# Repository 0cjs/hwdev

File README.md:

hwdev: cjs's Hardware Development Repo
======================================

__Note for developers:__ Please run `Test` before committing. But also:
- In order to avoid a lot of spurious changes on dev branches, `Test` will
  update renders only if you are commiting to the `main` branch. On dev
  branches, if you want to see/test renders, just use the `render` script
  directly. Ensure you bring commits to `main` and run `Test` there before
  pushing them and test them on `main`.
- If you see massive changes to renders in all projects when you run
  `Test`, you are probably running a different version of KiCad than
  normally used with this repo. Check the `kicad-version` file for changes
  and, if lower, upgrade, or if higher, discuss with the repo owner.

#### General Files and Directores

- `Test`: Top-level test script.
- `bin/`: Support programs and scripts.
  - `bin/render`: Given paths to `.kicad_sch` and `.kicad_pcb` files,
    renders PDF and Gerber versions of these to a `render/` dir at the same
    level as the directory containing the sch/pcb files. Run `bin/render -h`
    for more details.
  - `bin/ghdl-url`: Given a path to a file in a repo, return the fully
    resolved (i.e., not HTTP 302 redirects) GitHub download URL for it.
    (See the header comments in the file for more detail.)
- `kicad-version`: The version of KiCad used in the commit.
- `kicad-lib`: Contains the `0cjs-hwdev` KiCad symbol library, mainly
  vintage parts.

#### Project Directories

- [`drom`]: Ideas for a diode-ROM board.
- [`floppy-head-protector`]: PCB-only project to build a template to cut
  out cardboard head travel protectors for 5.25" floppy diskette drives.
- [`kp25tk`]: Configurable 25-key parallel keypad, with additional reset
  button and slide switch. The primary use is as a hex keypad interface to
  trainer boards, but it can serve a wide variety of purposes.
- [`rc6800`]: Variant of the RC6502 bus design, which is in turn a variant of
  the RC2014 bus.
- [`romread-adapter`]: Interface to allow reading of ROMs via the 8265
  PPI GPIO interface on a SuperAKI-80 SBC (or other similar system).
- [`romext-2364`]: A 2764 EPROM in this board outside the system is
  connected via a cable as a 2364 ROM in a socket in the system.
- [`tk85`]: Projects for the NEC TK-85 trainer board.

Project Files and Subdirectories
--------------------------------

Projects generally include the following files and subdirectories:
- `REAMDE.md`: A description of the project.
- `vis/`: Original diagrams, photos and other illustrations and
  visualisations of the project.
- `kicad/`: The KiCad design files (`.kicad_pro`, `.kicad_sch`, etc.).
- `render/`: Renderings from the KiCad design files, including a PDF of the
  schematic and Gerbers of the board design. These are usually generated
  via the top-level `render` script but may be created manually; see above.
  (Also see below about viewing board designs.)

### Revision Numbers

Project use revisions int the format _S-B_ where _S_ is the schematic
revision and _B_ is the board revision within that scheamtic. Either number
being suffixed with `dev` indicates that it's a development revision
heading towards that next revision, e.g., `2dev-3` is development towards
revision `2` of the schematic. (Revision `0` is always considered a
development revision towards revision `1`.)

The revision number is separately set and updated (in _File » Page
Settings…_) for the schematic and PCB. If you change the schematic from `2`
to `3` you will then manually need to change the PCB to from `2-3` to
`3-4dev`.

Release versions are tagged in Git with the project name and release,
separated by an underscore, e.g. `kp25tk_2-1`.

### Viewing Board Designs

The `$PROJECT/render/$PROJECT-jlcpcb.zip` contains a subset of Gerbers
designed for upload to [JLCPCB]. This file also serves as a way to view the
board design without having to load up KiCad: you can upload this file to
any of several web-based Gerber viewers. These include:

* __[PCBWay viewer]:__ Press the '+' button and upload the ZIP. Provides
  Gerber layers and 2D top and bottom board views. Saves the uploads so you
  need not upload again if you come back later.

* __[JLCPCB viewer]:__ Requires sign-in. Click "Add gerber file" at the
  middle left of the top page (or at the top of the order page) and then
  click "Gerber Viewer" at the lower right just below the small renders.
  provides Gerber layers and both 2D top/bottom 3D board renders.

* __[NextPCB viewer]:__ Click "Upload Files" and upload the ZIP. Provides
  Gerber layer views, error checking, and a PDF report download that
  includes 2D top/ bottom board views.

* __[Tracespace viewer]:__ An [open source][tracespace] viewer that can
  accept URLs to ZIP files of Gerbers. (This has been re-used by several
  PCB house websites and others.) Unfortunately, it does not follow HTTP
  302 redirects, so it doesn't work with "raw download" links from GitHub;
  you need to convert them to the `githubusercontent.com` link with
  the `bin/ghdl-url` program. Also, unfortunately, there seems to be no way
  to specify the download URL in a query string to have it automatically
  load the data by clicking on a link.

Viewers confirmed not to work with the ZIP file include the __[Altium 365
viewer].__ (These may work by uploading the individual files under the
`render/$PROJECT-gerber/` directory.)

<!-------------------------------------------------------------------->
[`drom`]: ./drom/
[`floppy-head-protector`]: ./floppy-head-protector/
[`kp25tk`]: ./kp25tk/
[`rc6800`]: ./rc6800/
[`romread-adapter`]: ./romread-adapter/
[`romext-2364`]: ./romext-2364/
[`tk85`]: ./tk85/

[Altium 365 viewer]: https://www.altium.com/viewer/
[JLCPCB viewer]: https://cart.jlcpcb.com/quote
[JLCPCB]: https://jlcpcb.com/
[NextPCB viewer]: https://www.nextpcb.com/free-online-gerber-viewer.html
[PCBWay viewer]: https://www.pcbway.com/project/OnlineGerberViewer.html
[Tracespace viewer]: https://tracespace.io/view/
[tracespace]: https://github.com/tracespace/tracespace

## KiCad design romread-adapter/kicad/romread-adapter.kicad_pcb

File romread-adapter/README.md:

ROM Reading Adapter
===================

You can download [the schematic in PDF format][dl-sch] and [a ZIP of the
Gerbers][dl-jlc]. The latter has been tested with JLCPCB, and you can also
give that URL to [tracespace.io] to view them.

This board allows a host device to read up to 42-pin through-hole DIP ROMs
with any arbitrary pinout. The host device will typically be a computer
that can supply ground and +5V, and has at least two Intel [8255] PPIs
(Programmable Peripheral Interface chips) that will be connected to the
address, data and select pins of the ROM.

The header is designed to connect to the the CN3 connector of an
[SuperAKI-80 SBC], connecting it to the 8265 that provides the equivalent
of two 8255 chips. However, via different cables and adapters (supplied by
the user) it can be connected to any system providing equivalent
functionality.

Usage
-----

The board has three main parts.

#### ZIF Socket

The ROM should be inserted in at the bottom of the 42-pin ZIF socket at the
left, with pin 1 towards the top.

#### Workspace Area

The centre of the board is the workspace area, consisting of two columns of
.1" header pins connected to the pins of the ROM device in the ZIF socket
("ROM pins") and separate pins connected to the address outputs, positive
and negative chip select outputs, and data inputs of the host device ("host
pins"). Between these two columns the silk screen indicates the pin numbers
for 24-, 28- and 32-pin ROM devices.

The 23 pins directly adjacent to the ZIF socket pins are "default pins,"
host pins assigned per the JEDEC standard pinouts for 24- and 28-pin ROMs
and EPROMs. When reading common devices, you can use jumpers to connect
these to the adjacent ROM pins; these typically will not need to be changed
unless you're reading a non-JEDEC device.

ROM pins pins without an adjacent default pin either have functions varying
between JEDEC standard ROM devices or there is no JEDEC common default for
them. These should be connected with "dupont" jumper wires to the headers
around the edge of the board that give access to ground, +5V, positive and
negative chip select outputs, address outputs, and data inputs.

#### Host Header

The host header connects the host via a 50-pin ribbon cable. For a
SuperAKI-80 board this can be connected directly to the CN3 connector; for
other boards you'll need to wire your own cable or adapter.

For the SuperAKI-80, the connections are as follows:

    SuperAKI-80     ROM Reader Board Host Signals
    ────────────────────────────────────────────────────────────
    VCC             VCC
    GND             GND
    PPI 0-A 0-7     A0-A7
    PPI 0-B 0-7     A8-A15
    PPI 0-C 0-3     A16-A19
            4,5     n/c
            6       CS (positive logic chip select)
            7       C̅S̅ (negative-logic chip select)
    PPI 1-A 0-7     D0-D7
    PPI 1-B 0-7     D9-D14
    PPI 1-C 0-7     n/c

#### Software

Software to read ROMs has not yet been developed.

Design Notes
------------

### PCB DRC Warnings and Exclusions

A number of PCB DRC warnings are ignored. The reasons are:
- "Adjacent header pins" courtyard overlaps on JR2 and JR3: In the work
  area the header pins intended for use with "default" jumpers for most
  ROMs the headers must be side by side in order to place the jumpers
  acrosss the pins.
- "Work area default jumpers" silkscreen overlap on JR2 and JR3: As with
  the work area header pins courtyard overlaps above.
- "ZIF socket at edge" silkscreen off edge of board: The ZIF socket is at
  the left edge of the board, causing a bit of the left edge of silk screen
  for the lever hinge to be cut off. This isn't a problem; enough is still
  there that the placement of the ZIF socket is clear.

<!-------------------------------------------------------------------->
[dl-jlc]: https://raw.githubusercontent.com/0cjs/hwdev/dev/cjs/25g03/rom-read-adapter/romread-adapter/render/romread-adapter-jlcpcb.zip
[dl-sch]: https://raw.githubusercontent.com/0cjs/hwdev/dev/cjs/25g03/rom-read-adapter/romread-adapter/render/romread-adapter-sch.pdf
[tracespace.io]: https://tracespace.io/view/

[SuperAKI-80 SBC]: https://akizukidenshi.com/goodsaffix/A003_SuperAKI-80.pdf
[8255]: https://en.wikipedia.org/wiki/Intel_8255

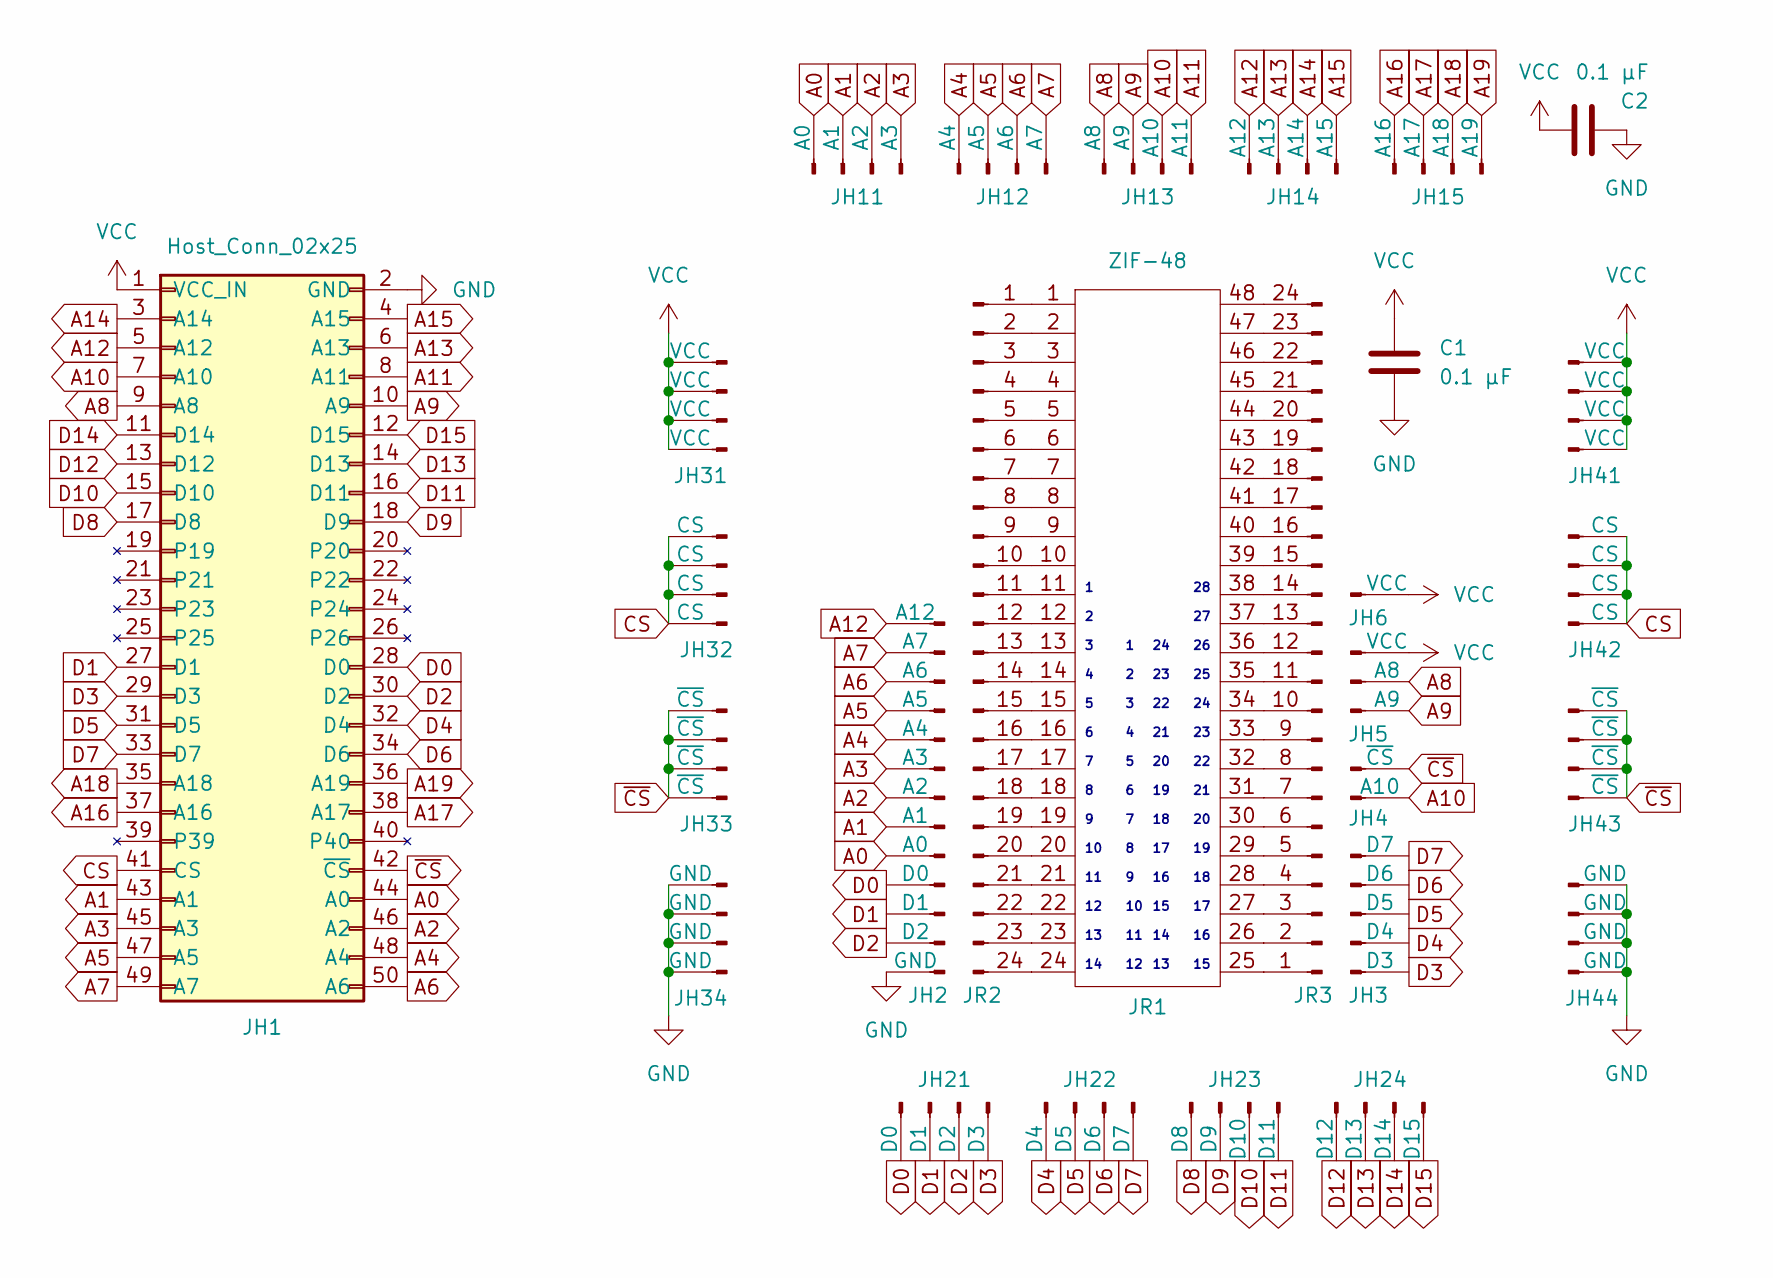
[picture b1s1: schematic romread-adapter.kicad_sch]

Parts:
C1, C2: 0.1 μF; C_Axial_L3.8mm_D2.6mm_P10.00mm_Horizontal
JH1: Host_Conn_02x25; PinHeader_2x25_P2.54mm_Vertical
JH2: Conn_01x13_Pin; PinHeader_1x13_P2.54mm_Vertical
JH3: Conn_01x05_Pin; PinHeader_1x05_P2.54mm_Vertical
JH4: Conn_01x02_Pin; PinHeader_1x02_P2.54mm_Vertical
JH5: Conn_01x03_Pin; PinHeader_1x03_P2.54mm_Vertical
JH6: Conn_01x01_Pin; PinHeader_1x01_P2.54mm_Vertical
JH11, JH12, JH13, JH14, JH15, JH21, JH22, JH23, JH24, JH31, JH32, JH33, JH34, JH41, JH42, JH43, JH44: Conn_01x04_Pin; PinHeader_1x04_P2.54mm_Vertical
JR1: ZIF-48; DIP_Socket-48_W11.9_W12.7_W15.24_W17.78_W18.5
JR2, JR3: Conn_01x24_Pin; PinHeader_1x24_P2.54mm_Vertical

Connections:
A0: JH1.44 (A0), JH2.9 (A0), JH11.1 (A0)
A1: JH1.43 (A1), JH2.8 (A1), JH11.2 (A1)
A2: JH1.46 (A2), JH2.7 (A2), JH11.3 (A2)
A3: JH1.45 (A3), JH2.6 (A3), JH11.4 (A3)
A4: JH1.48 (A4), JH2.5 (A4), JH12.1 (A4)
A5: JH1.47 (A5), JH2.4 (A5), JH12.2 (A5)
A6: JH1.50 (A6), JH2.3 (A6), JH12.3 (A6)
A7: JH1.49 (A7), JH2.2 (A7), JH12.4 (A7)
A8: JH1.9 (A8), JH5.2 (A8), JH13.1 (A8)
A9: JH1.10 (A9), JH5.1 (A9), JH13.2 (A9)
A10: JH1.7 (A10), JH4.1 (A10), JH13.3 (A10)
A11: JH1.8 (A11), JH13.4 (A11)
A12: JH1.5 (A12), JH2.1 (A12), JH14.1 (A12)
A13: JH1.6 (A13), JH14.2 (A13)
A14: JH1.3 (A14), JH14.3 (A14)
A15: JH1.4 (A15), JH14.4 (A15)
A16: JH1.37 (A16), JH15.1 (A16)
A17: JH1.38 (A17), JH15.2 (A17)
A18: JH1.35 (A18), JH15.3 (A18)
A19: JH1.36 (A19), JH15.4 (A19)
CS: JH1.41 (CS), JH32.1 (CS), JH32.2 (CS), JH32.3 (CS), JH32.4 (CS), JH42.1 (CS), JH42.2 (CS), JH42.3 (CS), JH42.4 (CS)
D0: JH1.28 (D0), JH2.10 (D0), JH21.1 (D0)
D1: JH1.27 (D1), JH2.11 (D1), JH21.2 (D1)
D2: JH1.30 (D2), JH2.12 (D2), JH21.3 (D2)
D3: JH1.29 (D3), JH3.1 (D3), JH21.4 (D3)
D4: JH1.32 (D4), JH3.2 (D4), JH22.1 (D4)
D5: JH1.31 (D5), JH3.3 (D5), JH22.2 (D5)
D6: JH1.34 (D6), JH3.4 (D6), JH22.3 (D6)
D7: JH1.33 (D7), JH3.5 (D7), JH22.4 (D7)
D8: JH1.17 (D8), JH23.1 (D8)
D9: JH1.18 (D9), JH23.2 (D9)
D10: JH1.15 (D10), JH23.3 (D10)
D11: JH1.16 (D11), JH23.4 (D11)
D12: JH1.13 (D12), JH24.1 (D12)
D13: JH1.14 (D13), JH24.2 (D13)
D14: JH1.11 (D14), JH24.3 (D14)
D15: JH1.12 (D15), JH24.4 (D15)
GND: C1.2, C2.2, JH1.2 (GND), JH2.13 (GND), JH34.1 (GND), JH34.2 (GND), JH34.3 (GND), JH34.4 (GND), JH44.1 (GND), JH44.2 (GND), JH44.3 (GND), JH44.4 (GND)
unnamed: JR1.1, JR2.1
unnamed: JR1.2, JR2.2
unnamed: JR1.3, JR2.3
unnamed: JR1.4, JR2.4
unnamed: JR1.5, JR2.5
unnamed: JR1.6, JR2.6
unnamed: JR1.7, JR2.7
unnamed: JR1.8, JR2.8
unnamed: JR1.9, JR2.9
unnamed: JR1.10, JR2.10
unnamed: JR1.11, JR2.11
unnamed: JR1.12, JR2.12
unnamed: JR1.13, JR2.13
unnamed: JR1.14, JR2.14
unnamed: JR1.15, JR2.15
unnamed: JR1.16, JR2.16
unnamed: JR1.17, JR2.17
unnamed: JR1.18, JR2.18
unnamed: JR1.19, JR2.19
unnamed: JR1.20, JR2.20
unnamed: JR1.21, JR2.21
unnamed: JR1.22, JR2.22
unnamed: JR1.23, JR2.23
unnamed: JR1.24, JR2.24
unnamed: JR1.25, JR3.1 (Pin_25)
unnamed: JR1.26, JR3.2 (Pin_26)
unnamed: JR1.27, JR3.3 (Pin_27)
unnamed: JR1.28, JR3.4 (Pin_28)
unnamed: JR1.29, JR3.5 (Pin_29)
unnamed: JR1.30, JR3.6 (Pin_30)
unnamed: JR1.31, JR3.7 (Pin_31)
unnamed: JR1.32, JR3.8 (Pin_32)
unnamed: JR1.33, JR3.9 (Pin_33)
unnamed: JR1.34, JR3.10 (Pin_34)
unnamed: JR1.35, JR3.11 (Pin_35)
unnamed: JR1.36, JR3.12 (Pin_36)
unnamed: JR1.37, JR3.13 (Pin_37)
unnamed: JR1.38, JR3.14 (Pin_38)
unnamed: JR1.39, JR3.15 (Pin_39)
unnamed: JR1.40, JR3.16 (Pin_40)
unnamed: JR1.41, JR3.17 (Pin_41)
unnamed: JR1.42, JR3.18 (Pin_42)
unnamed: JR1.43, JR3.19 (Pin_43)
unnamed: JR1.44, JR3.20 (Pin_44)
unnamed: JR1.45, JR3.21 (Pin_45)
unnamed: JR1.46, JR3.22 (Pin_46)
unnamed: JR1.47, JR3.23 (Pin_47)
unnamed: JR1.48, JR3.24 (Pin_48)
VCC: C1.1, C2.1, JH1.1 (VCC_IN), JH5.3 (VCC), JH6.1 (VCC), JH31.1 (VCC), JH31.2 (VCC), JH31.3 (VCC), JH31.4 (VCC), JH41.1 (VCC), JH41.2 (VCC), JH41.3 (VCC), JH41.4 (VCC)
~CS: JH1.42 (~CS), JH4.2 (~CS), JH33.1 (~CS), JH33.2 (~CS), JH33.3 (~CS), JH33.4 (~CS), JH43.1 (~CS), JH43.2 (~CS), JH43.3 (~CS), JH43.4 (~CS)

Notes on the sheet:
28 27 26 25 24 23 22 21 20 19 18 17 16 15
1 2 3 4 5 6 7 8 9 10 11 12
24 23 22 21 20 19 18 17 16 15 14 13
1 2 3 4 5 6 7 8 9 10 11 12 13 14

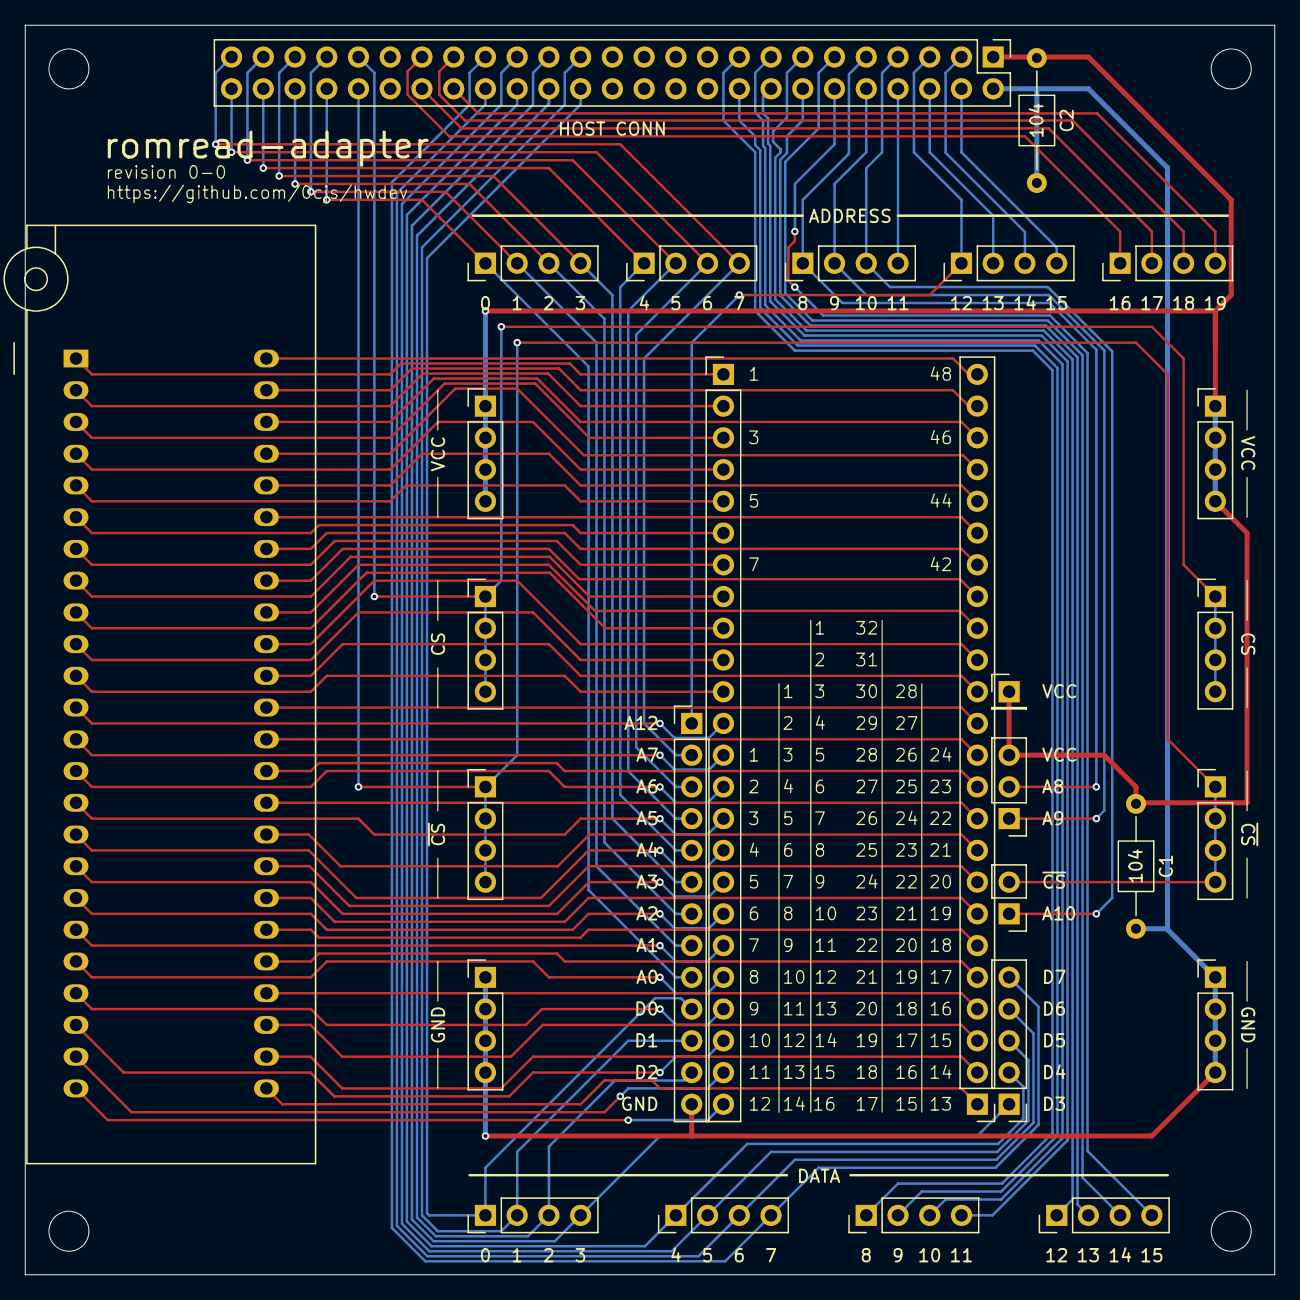
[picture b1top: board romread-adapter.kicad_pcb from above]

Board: 2 copper layers, 100.0 x 100.0 mm, 28 parts (0 on the bottom side), 88 nets.

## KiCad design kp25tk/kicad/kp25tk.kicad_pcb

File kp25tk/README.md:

KP25TK: 25-key Hex Keyboard
===========================

For ease of reference, this repository includes a `render/` subdirectory
containing some files generated from the `kicad/` files. __Bump version
numbers and regenerate these if you change the KiCad source.__
- [`kp25tk-sch.pdf`]: Schematic, generated via `File » Plot…` to PDF output.
- [`kp25tk-pcb.pdf`]: PCB, generated via File » Print…, enabling all layers,
  setting to portrait format and then printing to a file.
- [`kp25tk-render.png`]: PCB 3D render.
- [`kp25tk-silkscreen.png`]:
- [`kp25tk-tracks.png`]:

Contents:
- [Description](#description)
  - [Connections](#connections)
- [Components](#components)
  - [Key Swiches](#key-switches)
- [Theory of Operation](#theory-of-operation)
  - [Power Inputs](#power-inputs)
  - [Keypad Matrix](#keypad-matrix)
  - [NMI, Reset and Slide Switch Outputs](#nmi-reset-and-slide-switch-outputs)

Description
-----------

This 25-key 5×5 keyboard is similar to that on the [NEC TK-85].
with the following features.

* Power: +5V Vcc and GND from host system
* Matrix:
  - 3 row select input: ground one row to select
  - 8 row column output: rows pulled up to Vcc and pulled down by switch
  - 4×4 layout for hex digits `0` to `F`
  - 4 keys at the top and 4 keys at the right for commands
* 3 independent debounced switches:
  - Debounce time can be configured by changing a resistor value (see below).
  - All 3 provide positive and negative logic outputs.
  - 1 key at upper right hand corner of switch array for NMI interrupt
  - 1 tactile switch for RESET
  - 1 slide switch for a user-selected function

### Connections

The board is connected to the scanning device via a 2 row × 13 column
.1"-pitch male header ("Host"), usually used with a ribbon cable and IDC
female connector. The header is unshrouded to allow the use of smaller than
13 column connectors when the full 26 pins are not needed. (Though we
suggest _always_ using a 26P connector on the keypad side and simply using
a narrower ribbon cable that does not take up the full width of the
connector.)

The connector pin layout is configured via wire-wrapping or jumpering (with
"dupont" female-female jumper wires) individual 1-row header pins for each
function group to a second 2×13 header ("Config") that parallels the first.
This allows setting the ribbon cable connector pinout to match a wide
variety of scanning devices. The function groups are:

* Power input: 2:GND, 1:+5V
* Row select input: 3:row 2, 2:row 1, 1:row 0
* Column output: 8:column 7, ..., 1:column 0
* NMI key output: 2:/NMI (negative logic), 1:NMI (positive logic)
* RESET button output: 2:/RESET (negative logic), 1:RESET (positive logic)
* Slide switch output:
  -   UP: 2=low, 1=high
  - DOWN: 2=high, 1=low

### Design Goals

- Be fully configurable so it can work with almost any system.
- Do configuration in a way that it can be changed later.
- Provide a full hex keypad with additional keys for functions and some
  debounced switches for direct (non-scanned) functions.
- Have a physical layout that parallels the logical layout in order to make
  tracing the operation (whether for understanding or debugging) as easy as
  possible, even for novices to electronics.
- Use only through-hole parts to make soldering and modification as easy as
  possible.
- Be as compact as reasonably possible while meeting the other goals above.

Components
----------

### Key Switches

Currently planned are [Outemu "Tactile Brown"][keysw] (AliExpress) key
switches, which are (allegedly) compatible with Cherry MX and "CIY"
sockets.

These [Kailh switch sockets][kailh] (Adafruit) for MX-compatible mechanical
keys may be useful. They still need mechanical support, but the Adafruit
description says that a bit of hot glue or epoxy will do the trick.

Theory of Operation
-------------------

Component Summary:
- C[123], R[123], D[123], U1: Debounce and inversion circuitry for the
  `NMI` key, `RESET` button, and slide `SWITCH`, respectively.
- R[45], D[45]: Current-limiting resistors and LEDs for `PWR` (Vcc/GND
  present) and `SWLED` (slide switch ON) indicators, respectively.

### Host Connector and Configuration Headers

The 2×13 pin __Host__ header is connected to the host that will scan the
keypad. This is typically done with a ribbon cable with IDC connectors on
each end. Not all 26 pins need be used, but to help avoid pin interference
and misconnections it's best to use a 26-pin IDC connector on the keypad
end of the cable, even if a ribbon cable with fewer conductors is used.

The 2×13 __Config__ header pins are connected to the same-numbered Host
header pins; the builder needs to connect these to the function group
pins below. Wire-wrap is the most reliable way of doing this, but jumper
wires with "dupont"-style female connectors may also be used.

### Power Inputs

GND and +5V must be supplied from the host. (This is normally supplied
on the Host header, and then wired from the Config header to the `VCC_IN`
and `GND_IN` header pins.)

+5V is used to power the Schmitt inverters that debounce and invert the NMI
key, RESET button and slide switch. If only the keypad (less NMI key) is
used, +5V is not necessary.

A current-limiting resistor R4 (1K5) and power LED D4 indicate that the
board is powered. The current-limiting resistor is relatively high value so
that the LED isn't distractingly bright.

### Keypad Matrix

Each of the three row select inputs, `ROWSEL0`, `ROWSEL1`, `ROWSEL2`
connects to the corresponding row line for the keypad. When scanning, each
row in turn is driven low by the host, which then scans that row using the
column outputs.

Each column line is pulled high by its pull-up resistor when no key in that
column is pressed; this will read as `1` on the corresponding column output.
When a key in a _non-scanned_ row (row high or floating) is pressed, this
does not change. When a key in the _scanned_ row is pressed, the low row
sinks current through the diode and the closed keyswitch, bringing the
column low.

#### Keypad Pull-up Resistor Values

The keypad relies on the ability of the host driving the row select inputs
to to pull them down to 0 V, and do so reasonably quickly. Host drivers'
ability to do this varies, and the additional capacitance introduced by the
wiring connecting the keypad to the host, and the keys themselves, can
degrade this.

The 22K values chosen for the resistors give a fairly weak pull-up that's
still higher than other designs without a cable between the keyboard row
drivers and column inputs of the host. The resistor pack is in a socket to
allow changing the value.

If you are getting intermittent or no response from pressing keys, the
pull-up is too strong and you should try a _higher_ resistance, such as 33K
or 47K.

If you are getting lengthened or repeated key presses, the pull-up is too
weak and you should try a _lower_ resistance, such as 10K or 4K7.

#### Keypad Matrix Diodes

The diodes in the matrix serve two purposes.

First, they prevent shorts between the row inputs that would likely damage
the device driving them. Without the diodes, two switches held down on the
same column when one row is low short the low row to the high row.
(Consider, e.g., low row 0 → closed `KEY00` → pulls column 0 low → closed
`KEY08` pulls row 1 low. This is blocked by the diodes between `KEY08` and
row 1.) In keyboards without a diode on each key in the matrix, a diode on
each row line (cathode toward the row select input) would be required
instead.

Second, They prevent "ghost keys" when two keys in one column and one key
in the same row as either are pressed. Without the diodes, If `KEY00`,
`KEY01` and `KEY08` are pressed and `ROWSEL1` is low:
1. Low row 1 connects to column 0 via closed `KEY08`, pulling column 0 low.
2. Low column 0 connects to row 0 via closed `KEY00`, pulling row 0 low.
3. Low row 0 connects to column 1 via closed `KEY01`, pulling column 1 low.
4. The system scanning row 1 sees column 1 low, though `KEY09` is not
   pressed.
The diode between `KEY00` and row 0 prevents the connection in point 2.

Schottky diodes are used instead of silicon diodes to reduce the forward
voltage drop. These _must_ be used for reliability, as the maximum ouput
voltage for a 5V TTL low signal is 0.5 V, and a silicon diode would exceed
this, not bringing the column lines low enough to meet that specification.

This is still out of spec for 5V CMOS output voltage, but well within the
1.5 V maximum that CMOS parts must accept at input as a low voltage.

### NMI, Reset and Slide Switch Outputs

#### Debounce

The upper-right key on the keypad is the "NMI" button. Above the keypad and
to the right is a momentary-contact button, "Reset." Above the keypad and
to the left is a slide switch, "switch" (which may also be called "single
step"). These all provide debounced positive and negative signals separate
from the key matrix. They may be used for any purpose; the names merely
represent typical uses.

Each is debounced via a resistor-capacitor pair, with a diode for
overvoltage protection. R1/C1/D1 are used for NMI; R2/C2/D2 for Reset, and
R3/C3/D3 for the switch. All three operate in exactly the same way, though
you may vary the resistor values for each to give different debounce time
constants if needed. (This will normally not be necessary.)

The debounce works as follows.

When the switch is open (not pressed), the input to the 74x14 Schmitt
trigger gate is raised to +5 V through resistor R1. However, reaching +5 V
will be delayed because C2 must be charged first. (The rate of charge is
[standard for an RC circuit][rc].) Once the charge on R1 has reached the
Vt+ level of the '14 (typically ~1.6 V), the positive logic output of the
switch will go low and the negative logic output of the switch will go
high.

When the switch is pressed, it will short the '14 input to ground, quickly
making it fall below the Vt- level of the '14 (typically ~0.8 V) and the
positive logic output of the switch will switch to high and the negative
logic output will switch to low. This state will remain until the switch is
released, at which point the capacitor will start charging through the RC
circuit as above, eventually reaching the point where the positive logic
output goes low and the negative logic output goes high.

The time constant of R1×C1 determines how long the switch will take to be
released; with the specified 10 kΩ resistor and 0.1 μF capacitor, this will
be about 1 millisecond. The resistor can be changed to a higher value (e.g.
100 kΩ = 10 ms) or a lower value (e.g., 1 kΩ = 100 μs) if necessary.

The Schottky diode (typically 1N5819 or 1N5817) from the gate input to the
+5 V source ensures that the voltage at the gate input never exceeds the
power supply Vcc level plus the forward voltage drop of 0.3 V.

#### Switch LED

The switch additionally has an LED that is illuminated when it's active (in
the "up" position) and extinguished when it's inactive (in the "down"
position).

A current-limiting resistor R5 (1K5) and power LED D5 indicate when the
slide switch is active (up). The current-limiting resistor is relatively
high value so that the LED isn't distractingly bright and to minimise
load on the U1F buffer output.

We avoid placing the LED on the switch side of U1F to avoid any
interference with the debounce logic. That leaves the options of the
postive-logic U1F output and the negative-logic U1E output: we choose the
latter because LS logic is much better at sinking current than sourcing it.

<!-------------------------------------------------------------------->
[`kp25tk-pcb.pdf`]: ./render/kp25tk-pcb.pdf
[`kp25tk-render.png`]: ./render/kp25tk-render.png
[`kp25tk-sch.pdf`]: ./render/kp25tk-sch.pdf
[`kp25tk-silkscreen.png`]: ./render/kp25tk-silkscreen.png
[`kp25tk-tracks.png`]: ./render/kp25tk-tracks.png

[NEC TK-85]: https://gitlab.com/retroabandon/tk80-re
[kailh]: https://www.adafruit.com/product/4958
[keysw]: https://www.aliexpress.com/item/1005004285423123.html

[rc]: https://en.wikipedia.org/wiki/Rc_circuit

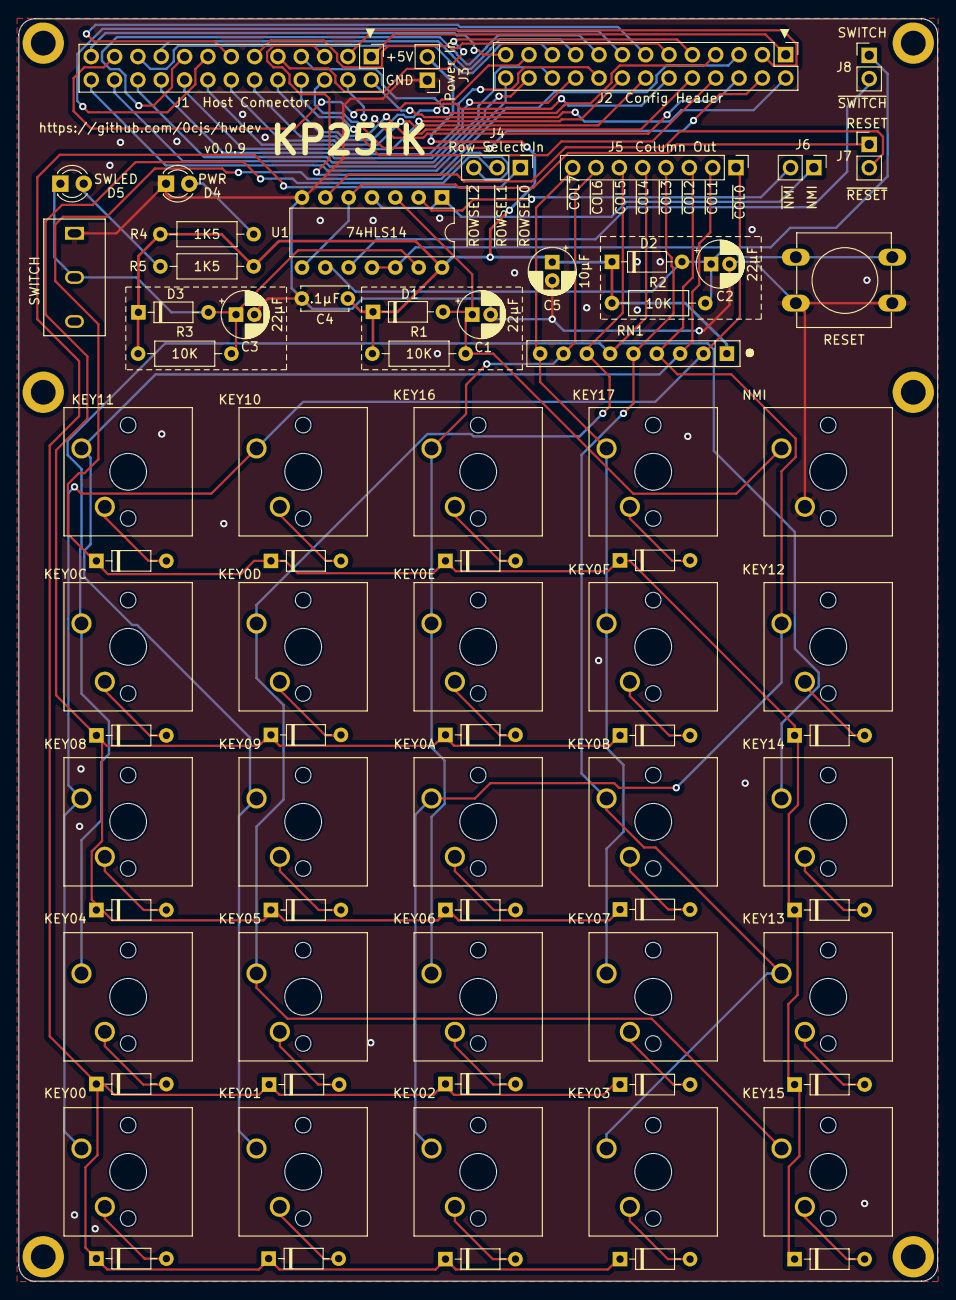
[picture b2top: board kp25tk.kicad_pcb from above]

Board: 2 copper layers, 100.0 x 137.4 mm, 101 parts (0 on the bottom side), 74 nets.

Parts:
C1, C2, C3: 22µF; CP_Radial_D5.0mm_P2.00mm
C4: .1µF; C_Disc_D5.0mm_W2.5mm_P5.00mm
C5: 10µF; CP_Radial_D5.0mm_P2.00mm
D1, D2, D3, D8, D9, D10, D11, D12, D13, D14, D15, D16, D17, D18, D19, D20, D21, D22, D23, D24, D25, D26, D27, D28, D29, D30, D31: 1N5819; D_DO-35_SOD27_P7.62mm_Horizontal
D4: PWR; LED_D3.0mm
D5: SWLED; LED_D3.0mm
J1: Host Connector; PinHeader_2x13_P2.54mm_Vertical
J2: Config Header; PinHeader_2x13_P2.54mm_Vertical
J3: Power In; PinHeader_1x02_P2.54mm_Vertical
J4: Row Select In; PinHeader_1x03_P2.54mm_Vertical
J5: Column Out; PinHeader_1x08_P2.54mm_Vertical
J6: NMI Out; PinHeader_1x02_P2.54mm_Vertical
J7: Reset Out; PinHeader_1x02_P2.54mm_Vertical
J8: Switch; PinHeader_1x02_P2.54mm_Vertical
R1, R2, R3: 10K; R_Axial_DIN0207_L6.3mm_D2.5mm_P10.16mm_Horizontal
R4, R5: 1K5; R_Axial_DIN0207_L6.3mm_D2.5mm_P10.16mm_Horizontal
RN1: 22K; R_Array_SIP9
SW0: KEY00; SW_Cherry_MX_1.00u_PCB
SW1: KEY01; SW_Cherry_MX_1.00u_PCB
SW2: KEY02; SW_Cherry_MX_1.00u_PCB
SW3: KEY03; SW_Cherry_MX_1.00u_PCB
SW4: KEY04; SW_Cherry_MX_1.00u_PCB
SW5: KEY05; SW_Cherry_MX_1.00u_PCB
SW6: KEY06; SW_Cherry_MX_1.00u_PCB
SW7: KEY07; SW_Cherry_MX_1.00u_PCB
SW8: KEY08; SW_Cherry_MX_1.00u_PCB
SW9: KEY09; SW_Cherry_MX_1.00u_PCB
SW10: KEY0A; SW_Cherry_MX_1.00u_PCB
SW11: KEY0B; SW_Cherry_MX_1.00u_PCB
SW12: KEY0C; SW_Cherry_MX_1.00u_PCB
SW13: KEY0D; SW_Cherry_MX_1.00u_PCB
SW14: KEY0E; SW_Cherry_MX_1.00u_PCB
SW15: KEY0F; SW_Cherry_MX_1.00u_PCB
SW16: KEY10; SW_Cherry_MX_1.00u_PCB
SW17: KEY11; SW_Cherry_MX_1.00u_PCB
SW18: KEY12; SW_Cherry_MX_1.00u_PCB
SW19: KEY13; SW_Cherry_MX_1.00u_PCB
SW20: KEY14; SW_Cherry_MX_1.00u_PCB
SW21: KEY15; SW_Cherry_MX_1.00u_PCB
SW22: KEY16; SW_Cherry_MX_1.00u_PCB
SW23: KEY17; SW_Cherry_MX_1.00u_PCB
SW24: NMI; SW_Cherry_MX_1.00u_PCB
SW25: RESET; SW_PUSH-12mm
SW27: SWITCH; SW_MINI-SPDT-SW
SWKC0, SWKC1, SWKC2, SWKC3, SWKC4, SWKC5, SWKC6, SWKC7, SWKC8, SWKC9, SWKC10, SWKC11, SWKC12, SWKC13, SWKC14, SWKC15, SWKC16, SWKC17, SWKC18, SWKC19, SWKC20, SWKC21, SWKC22, SWKC23, SWKC24: Keycap; SW_Cherry_MX_Keycap_1.00u
U1: 74HLS14; DIP-14_W7.62mm

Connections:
+5V: C4.2, C5.1, D1.1 (K), D2.1 (K), D3.1 (K), J3.2 (VCC_IN), R1.1, R2.1, R3.1, R4.1, R5.1, RN1.1 (R1), U1.14 (VCC)
/HOST1: J1.1, J2.1
/HOST2: J1.2, J2.2
/HOST3: J1.3, J2.3
/HOST4: J1.4, J2.4
/HOST5: J1.5, J2.5
/HOST6: J1.6, J2.6
/HOST7: J1.7, J2.7
/HOST8: J1.8, J2.8
/HOST9: J1.9, J2.9
/HOST10: J1.10, J2.10
/HOST11: J1.11, J2.11
/HOST12: J1.12, J2.12
/HOST13: J1.13, J2.13
/HOST14: J1.14, J2.14
/HOST15: J1.15, J2.15
/HOST16: J1.16, J2.16
/HOST17: J1.17, J2.17
/HOST18: J1.18, J2.18
/HOST19: J1.19, J2.19
/HOST20: J1.20, J2.20
/HOST21: J1.21, J2.21
/HOST22: J1.22, J2.22
/HOST23: J1.23, J2.23
/HOST24: J1.24, J2.24
/HOST25: J1.25, J2.25
/HOST26: J1.26, J2.26
Earth: C1.2, C2.2, C3.2, C4.1, C5.2, D4.1 (K), J3.1 (GND_IN), SW24.2, SW25.2, SW27.1 (A), U1.7 (GND)
unnamed: C1.1, D1.2 (A), R1.2, SW24.1, U1.3
unnamed: C2.1, D2.2 (A), R2.2, SW25.1, U1.9
unnamed: C3.1, D3.2 (A), D5.1 (K), R3.2, SW27.2 (B), U1.13
unnamed: D4.2 (A), R4.2
unnamed: D5.2 (A), R5.2
unnamed: D8.2 (A), SW0.2
unnamed: D9.2 (A), SW1.2
unnamed: D10.2 (A), SW2.2
unnamed: D8.1 (K), D9.1 (K), D10.1 (K), D11.1 (K), D12.1 (K), D13.1 (K), D14.1 (K), D15.1 (K), J4.1 (~ROWSEL0)
unnamed: D11.2 (A), SW3.2
unnamed: D12.2 (A), SW4.2
unnamed: D13.2 (A), SW5.2
unnamed: D14.2 (A), SW6.2
unnamed: D15.2 (A), SW7.2
unnamed: D16.2 (A), SW8.2
unnamed: D16.1 (K), D17.1 (K), D18.1 (K), D19.1 (K), D20.1 (K), D21.1 (K), D22.1 (K), D23.1 (K), J4.2 (~ROWSEL1)
unnamed: D17.2 (A), SW9.2
unnamed: D18.2 (A), SW10.2
unnamed: D19.2 (A), SW11.2
unnamed: D20.2 (A), SW12.2
unnamed: D21.2 (A), SW13.2
unnamed: D22.2 (A), SW14.2
unnamed: D23.2 (A), SW15.2
unnamed: D24.2 (A), SW16.2
unnamed: D24.1 (K), D25.1 (K), D26.1 (K), D27.1 (K), D28.1 (K), D29.1 (K), D30.1 (K), D31.1 (K), J4.3 (~ROWSEL2)
unnamed: D25.2 (A), SW17.2
unnamed: D26.2 (A), SW18.2
unnamed: D27.2 (A), SW19.2
unnamed: D28.2 (A), SW20.2
unnamed: D29.2 (A), SW21.2
unnamed: D30.2 (A), SW22.2
unnamed: D31.2 (A), SW23.2
unnamed: J5.1 (~COL0), RN1.2 (R1.2), SW0.1, SW8.1, SW16.1
unnamed: J5.2 (~COL1), RN1.3 (R2.2), SW1.1, SW9.1, SW17.1
unnamed: J5.3 (~COL2), RN1.4 (R3.2), SW2.1, SW10.1, SW18.1
unnamed: J5.4 (~COL3), RN1.5 (R4.2), SW3.1, SW11.1, SW19.1
unnamed: J5.5 (~COL4), RN1.6 (R5.2), SW4.1, SW12.1, SW20.1
unnamed: J5.6 (~COL5), RN1.7 (R6.2), SW5.1, SW13.1, SW21.1
unnamed: J5.7 (~COL6), RN1.8 (R7.2), SW6.1, SW14.1, SW22.1
unnamed: J5.8 (~COL7), RN1.9 (R8.2), SW7.1, SW15.1, SW23.1
unnamed: J6.1 (NMI), U1.1, U1.4
unnamed: J6.2 (~NMI), U1.2
unnamed: J7.1 (RESET), U1.5, U1.8
unnamed: J7.2 (~RESET), U1.6
unnamed: J8.1 (SWITCH), U1.11, U1.12
unnamed: J8.2 (~SWITCH), U1.10

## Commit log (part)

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2023-07-19 hwdev: cjs's hardware development repo
2023-07-19 README: Repo title
2023-12-30 kp25tk/: KP25TK 25-key Hex Keyboard initial README and TODO
2023-12-30 kp25tk/kp25tk.pdf: Plot schematic to PDF
2023-12-30 kp25tk/TODO: Decoupling caps, diodes on COL lines
2024-01-01 kp25tk/kp25tk{,-sch}.pdf: Rename schematic export to distinguish it from PCB
2024-01-01 kp25tk/README: Add Theory of Operation section (incomplete)
2024-01-01 kp25tk/kp25tk-pcb.pdf: Printout of current PCB design
    This is done via File » Print…, enabling all layers, setting to portrait
    format and then printing to a file.
2024-01-01 kp25tk/ PCB: U-shaped config area; other cleanup
    - Configuration area is compactified by moving slide switch and reset
    outputs to the right of the config header, and power in to the left, and
    orienting these vertically.
    - Host Conector and Config Header were upside down; rotate them 180° so
    that pin 1 is on the right instead of the left.
    - Make silkscreen names "Host Connector" and "Config Header" horizontal.
2024-01-02 TODO: Column pull-up resistor change
2024-01-02 kp25tk/: v0.0.4 Use resistor array and greatly compactify top of PCB
2024-01-03 kp25tk/README: Make sch/pcb PDFs links, for convenience when browing on GitHub
2024-01-03 kp25tk/: v0.0.5 Schottky diodes, diodes in matrix
2024-01-05 kp25tk/README: Keypad theory of operation; tweak headings
2024-01-05 kp25tk/README: Link the kp25tk-render image
2024-01-06 kp25tk/kicad/kp25tk.kicad_pro: Change plot directory to `../`
    This still generates `kp25tk.pdf`, but at least it's in the same
    directory as the `kp25k-sch.pdf` that it needs to be renamed to.
2024-01-06 kp25tk//sch: Bump schematic (only) version number to 0.0.7
    We don't bump the PCB because it's not been updated from the schematic
    yet and the new LED has not been added.
    Also update the README to mention that we should remember to update the
    version numbers when updating the generated files.
2024-01-11 TODO: 1N5819 vs. 1N4148
2024-01-13 TODO: Review w/Edoardo
2024-01-23 drom/README: More references
2024-01-24 drom/README: Describe anode recovery
2024-02-27 kp25tk/: Release candidate 1
2024-04-16 kp25tk/README: Fix links to renders
2025-03-24 .gitignore fp-info-cache: W/KiCad 9.x, may be a file instead of a directory
2025-06-10 romext-2364/: External board with 2764 EEPROM fills internal 2364 ROM
2025-06-13 kp25tk/README: "Design goals"; misc. improvements; formatting improvements
2025-06-13 WIP kp25tk/: Cut off board to 100×100; plot Gerbers
    TODO: drill files
    - Instructions added to README.
    - Gerbers plotted to kicad/fab/.
    Extra files to get rid of or ignore:
    ?? kicad/_autosave-kp25tk.kicad_pcb
    ?? kicad/fab/report.txt
2025-06-18 submodule kicad-lib/kitspace: kitspace kicad_footprints library
2025-06-18 romext-2364 sch: Add 2764 from standard KiCad library
2025-06-22 .gitignore: Ignore more KiCad backups/autosaves; better sort
2025-07-02 lib/0cjs 2364: NEC mask ROM
    - Symbol organisation matches KiCad's standard 2764/27C64.
    - Includes link to datasheet on archive.org.
    - Uses the DIP-24W footprints from the standard KiCad libraries.
    - Assumes negative-logic chip select; this must be changed in the
    schematic to positive logic for systems expecting ROMs masked for
    positive-logic select.
2025-07-02 rom-read-adapter/ pro: README and empty KiCad project
    ../../kicad-lib/0cjs-hwdev added to project footprint libs in schematic
    editor, though I probably won't need it.
2025-07-04 TODO: Script generation of PDFs, etc.
2025-07-05 romext-2364 sch: Set plot directory to ../generated/
2025-07-05 romext-2364/kicad/romext-2364.kicad_{pro,sch,pcb}: Empty KiCad project
2025-07-05 hwdev.romext-2364: Add name, url and revision to title block
2025-07-05 romext-2364 sch: Complete schematic of basic version
    The "2364" is actually a socket J1, where the addr/data/select
    lines are outputs because this is wired to the socket on the
    PC-8001 motherboard.
    This is the simplest design that will work with the PC-8001 and
    an ST Microelectronics M2764A; it does not yet provide facilities
    to work with systems or EPROMs that vary how they use chip select
2025-07-05 romext-2364 pro: Plot dir generated/ → render/ (matches kp25tk)
2025-07-05 */render/*-sch.pdf: Regenerate
2025-07-07 */*-sch.pdf: Update to versions without creation date
    kp25tk-sch.pdf changes fairly extensively, probably due to the way
    that KiCad has changed its PDF generation over time. It looks the
    same when viewed excepting that the KiCad version in the title block
    has changed from 7.0.10 to 9.0.2.
2025-07-07 WIP fhp pcb: Central area and bottom tab
    This does not yet have the line between the two areas removed.
2025-07-09 WIP FHP: Shorten Y 3mm
    - It was 1mm too large
    - Remove 2 more mm because knife will cut a bit away from edge
    - Still need to do this for Y
2025-07-09 romext-2364/kicad/jlcpcb/: Gerbers generated by bouni plugin
    These were generated with the JLCPCB Tools from
    https://raw.githubusercontent.com/Bouni/bouni-kicad-repository/main/repository.json
2025-07-09 romext-2364 pcb: Rev 1.0 for release
2025-07-13 WIP FHP: Added centre circle and realign object 10mm XY
2025-07-13 WIP kicad-lib RRA: Created ZIF48 symbol
2025-07-14 WIP kicad RRA: Added Jumpers, header pins, power symbols
    - need to add CS and resize header pins
2025-07-21 romext-2364 pcb: Change U1/2764 to use standard library ZIF footprint
    Bumps PCB revision to 1-2dev.
    The footprint was hard to find[1]; one has to turn off the footprint
    filter to have it come up.
    This updates the schematic as well, but just the footprint assignment
    in it, so we don't need to bump the revision. (It does update the PDF,
    however, because that contains the footprint info in the internal
2025-07-21 render: Generate PDF schematics and Gerber PCB layouts
    This is currently run only manually because even if there have been
    no changes to the source files, it always generates changed output
    due to the creation date in the files. (This needs to be fixed before
    we start doing this automatically in `Test`.)
    Test no longer does the automatic schematic rendering; we're waiting
    for `render` to be fixed.
2025-07-21 README: We now use B-P revision numbers, not B.P
2025-07-21 floppy-head-protector: Revision 0-1; add to top-level README
2025-07-29 WIP rom-read-adapter sch: Start using pin headers
2025-08-04 romext-2364/README: Now tested; also note need for bypass cap
2025-08-05 WIP rom-read-adapter sch: Finish nets for J1 J4 connections
2025-08-06 WIP rom-read-adapter sch: Added J6.
2025-08-09 WIP rom-read-adapter sch: Completed Schematic
2025-08-14 render: Export LC_COLLATE=C; explain why we remove the jlcpcb.zip
    LC_COLLATE=C is to reduce non-determinism from Bash's (and other
    programs') sorting of filenames. For more information, see the
    comments in the code.
2025-08-14 render: Update files only if something other than creation date changed
    This is possibly a little fragile and likely could use more testing.
2025-08-14 render: Extract check_command()
2025-08-14 render,Test: Ensure kicad-version file is in $projdir, and document it
2025-08-14 */render/: Add full rendering of projects that didn't yet have it
2025-08-16 TEST kp25tk pcb: Move bottom edge cut up to get <100×100 board
    This is intended to get a cheap prototype from JLCPCB; we still get
    three rows of keys which is enough to test with.
    All the stuff outside the edge cut is still left there; we'll see if
    JLCPCB just ignores that or if we have to remove that too.
2025-08-16 WIP rom-read-adapter pcb: Add lkscreen for data pins
2025-08-16 lib sym ZIF48: Fix pins; add footprint filter and default footprint
    * We had a nameless, numberless, 49th pin that was clearly
    accidentally entered.
    * All pins should probably have names, so we named them 'Pin_N'.
    * The default footprint is our new
    DIP_Socket-48_W11.9_W12.7_W15.24_W17.78_W18.5 in our repo library,
    but we also match any DIP*W15.24* just in case you should, for some
2025-08-16 WIP rom-read-adapter pcb: Start PCB layout
2025-08-16 rom-read-adapter sch: ZIF symbol update from lib and footprint; pin updates
    The pin updates are for JR3 (the pin header connected directly to ZIF
    pins 25-48) where we had pins numbered from 25-48 on JR3 also numbered
    to match. Not clear if this was a problem, because we also had the
    connections between the ZIF and this header in a real mess, but it's
    now exactly pin-to-pin as it should always have been. Before we
    weren't seeing the correct connections on the PCB editor ratsnest; now
2025-08-16 WIP rom-read-adapter pcb: ROM connection area pin numbering
2025-08-16 TESTING kp25tk pcb: More tweaking to get down to < 99×99
    JLCPCB reads as 98.77 × 98.25 mm. And this does work for OCS NEP $1 shipping.
2025-08-18 WIP rom-read-adapter pcb: New routing approach
2025-08-19 WIP rom-read-adapter pcb: Finish routing address pins
2025-08-19 WIP rom-read-adapter pcb: More routing; hit default pins problem
    The default pins are in the way of getting ZIF socket pads connected
    ZIF work area pin pads. We may try doing only right side pins on top
    layer from this point on, and routing through the bottom layer for the
    left side pins.
2025-08-19 WIP rom-read-adapter pcb: Everything routed except bypass cap
    We need to figure out the best physical position for the bypass cap.
    Ideally it should be as close as possible to the device pins
    themselves, but we don't know which device pins are power; those are
    determined half way across the board in the work area. So maybe place
    it across the pin 12/24 GND and pin 24/24 VCC? Probably wants to be an
    axial in that case, perhaps positioned top-to-bottom in the RHS
2025-08-19 WIP rom-read-adapter: Replace disc cap with axial; all traces routed
    We've gone with the solution mentioned in the previous commit message,
    where we put an axial cap kinda-near the GND and VCC pins in the work
    area. It could be closer, by moving some traces, or even by putting it
    in between the socket pin connectors, though that would cover up lots
    of pin numbers. (Maybe try it on the bottom? Still would moving some
    traces to make room for the pads.)
2025-09-06 WIP rom-read-adapter pcb: Added mounting holes
2025-09-09 WIP rom-read-adapter pcb: Re-routing
2025-09-13 kicad-version: 9.0.2 → 9.0.3; Debian 13 has updated; re-render sch/Gerbers
2025-09-17 README: Test and KiCad versions; online gerber viewers; heading re-org; etc.
2025-09-17 README: Add tracespace.io Gerber viewer
2025-09-17 render → bin/render: Rename
    We have more scripts coming, so let's have a nice home for all of them.
2025-09-18 bin/ghdurl: Get fully resolved download URL for a GitHub file
    This gets download links for $PROJ/render/$PROJ-jlcpcb.zip files
    that will not result in any HTTP 302 redirects, allowing use with
    Gerber viewers such as tracespace.io that are unable to follow
    those redirects.
2025-09-18 romread-adapter/: ROM Reading Adapter for SuperAKI-80
2025-09-18 romread-adapter/README: Add download links for schematic and Gerbers
2025-09-18 romread-adapter: Host conn pin rename VCC_IN; enabled more warnings
    J1 changed to JH1, it should of been JH1 before and we don't know why.
2025-09-22 romread-adapter pcb: Add mounting holes
